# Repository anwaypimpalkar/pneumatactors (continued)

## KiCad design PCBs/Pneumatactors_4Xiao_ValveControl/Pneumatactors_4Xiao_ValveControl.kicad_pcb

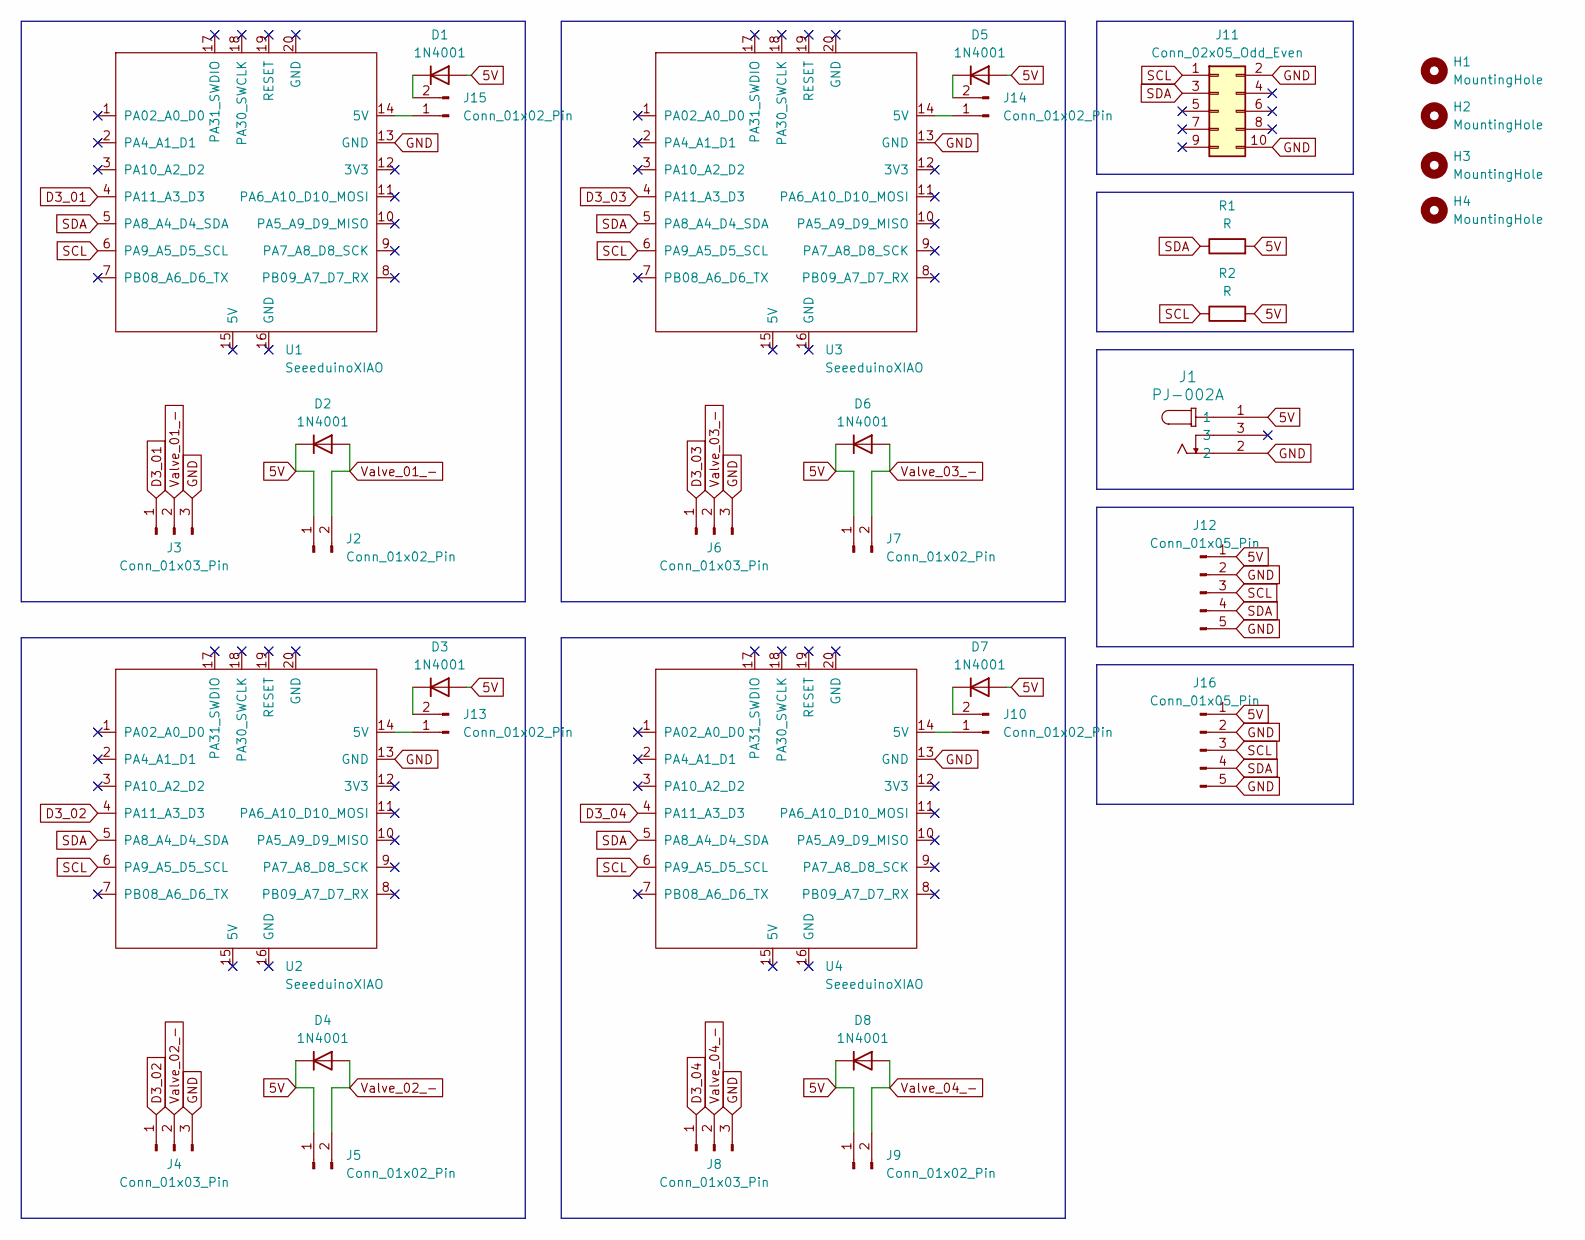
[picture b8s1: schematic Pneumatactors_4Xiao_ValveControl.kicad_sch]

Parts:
D1, D2, D3, D4, D5, D6, D7, D8: 1N4001; D_DO-41_SOD81_P10.16mm_Horizontal
H1, H2, H3, H4: MountingHole; MountingHole_3.2mm_M3_ISO14580_Pad
J1: PJ-002A; PJ-002A_CUD
J2, J5, J7, J9, J10, J13, J14, J15: Conn_01x02_Pin; PinHeader_1x02_P2.54mm_Vertical
J3, J4, J6, J8: Conn_01x03_Pin; PinHeader_1x03_P2.54mm_Vertical
J11: Conn_02x05_Odd_Even; PinHeader_2x05_P2.54mm_Vertical
J12, J16: Conn_01x05_Pin; PinHeader_1x05_P2.54mm_Vertical
R1, R2: R; R_Axial_DIN0207_L6.3mm_D2.5mm_P10.16mm_Horizontal
U1, U2, U3, U4: SeeeduinoXIAO; XIAO-Generic-Thruhole-14P-2.54-21X17.8MM

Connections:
5V: D1.2 (A), D2.1 (K), D3.2 (A), D4.1 (K), D5.2 (A), D6.1 (K), D7.2 (A), D8.1 (K), J1.1, J2.1, J5.1, J7.1, J9.1, J12.1, J16.1, R1.2, R2.2
D3_01: J3.1, U1.4 (PA11_A3_D3)
D3_02: J4.1, U2.4 (PA11_A3_D3)
D3_03: J6.1, U3.4 (PA11_A3_D3)
D3_04: J8.1, U4.4 (PA11_A3_D3)
GND: J1.2, J3.3, J4.3, J6.3, J8.3, J11.2, J11.10, J12.2, J12.5, J16.2, J16.5, U1.13 (GND), U2.13 (GND), U3.13 (GND), U4.13 (GND)
unnamed: D1.1 (K), J15.2
unnamed: D3.1 (K), J13.2
unnamed: D5.1 (K), J14.2
unnamed: D7.1 (K), J10.2
unnamed: J10.1, U4.14 (5V)
unnamed: J13.1, U2.14 (5V)
unnamed: J14.1, U3.14 (5V)
unnamed: J15.1, U1.14 (5V)
SCL: J11.1, J12.3, J16.3, R2.1, U1.6 (PA9_A5_D5_SCL), U2.6 (PA9_A5_D5_SCL), U3.6 (PA9_A5_D5_SCL), U4.6 (PA9_A5_D5_SCL)
SDA: J11.3, J12.4, J16.4, R1.1, U1.5 (PA8_A4_D4_SDA), U2.5 (PA8_A4_D4_SDA), U3.5 (PA8_A4_D4_SDA), U4.5 (PA8_A4_D4_SDA)
Valve_01_-: D2.2 (A), J2.2, J3.2
Valve_02_-: D4.2 (A), J4.2, J5.2
Valve_03_-: D6.2 (A), J6.2, J7.2
Valve_04_-: D8.2 (A), J8.2, J9.2

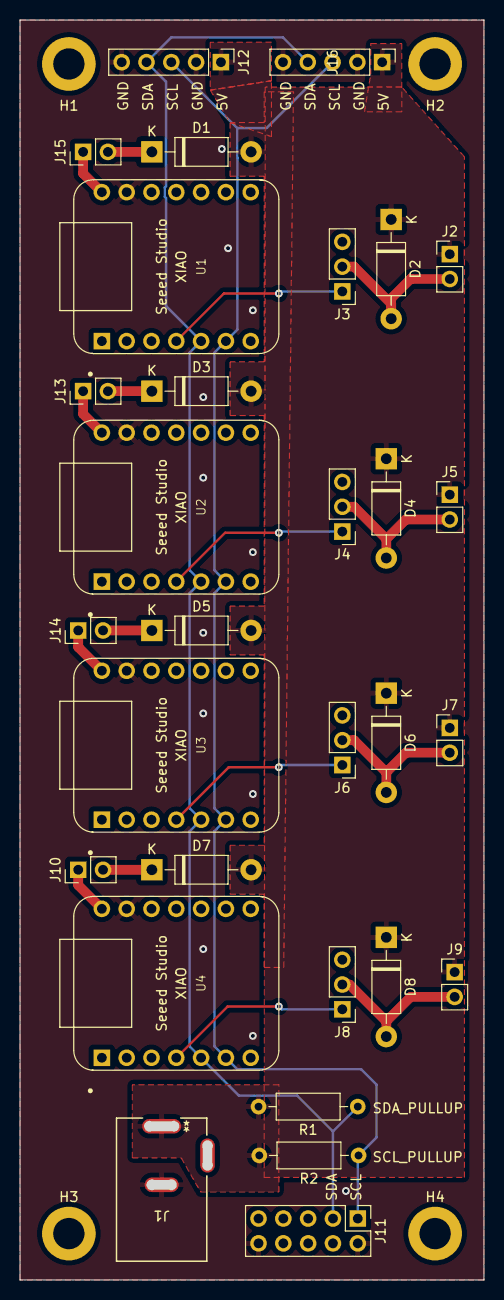
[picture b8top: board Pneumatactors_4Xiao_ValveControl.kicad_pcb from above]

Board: 2 copper layers, 46.6 x 128.1 mm, 34 parts (0 on the bottom side), 20 nets.

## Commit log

2025-03-06 initial file dump
2025-03-07 2025-03-07 00:00:05
2025-03-10 2025-03-10 12:00:02
2025-03-11 2025-03-11 00:00:03
2025-03-12 updated virtual task
2025-03-12 setup on PC complete
2025-03-14 2025-03-14 12:05:54
2025-03-16 quanser setup
2025-03-18 integrated emg!!
2025-03-19 emg integrated!!
2025-03-19 fixed aardvark api call
2025-03-19 2025-03-19 18:00:02
2025-03-19 PCB works!!
2025-03-20 emg better
2025-03-20 2025-03-20 12:00:02
2025-03-23 2025-03-23 18:00:03
2025-03-23 PCBs fixed
2025-03-24 2025-03-24 00:00:04
2025-03-25 2025-03-25 00:00:03
2025-03-25 2025-03-25 12:00:03
2025-03-27 2025-03-27 00:00:06
2025-03-27 2025-03-27 18:00:04
2025-03-28 changes made
2025-03-29 characterization 1 curve
2025-06-20 2025-03-29 18:00:06
2025-06-24 trials created
2025-06-25 app update
2025-07-01 U18 :)
2025-07-01 U18 :))
